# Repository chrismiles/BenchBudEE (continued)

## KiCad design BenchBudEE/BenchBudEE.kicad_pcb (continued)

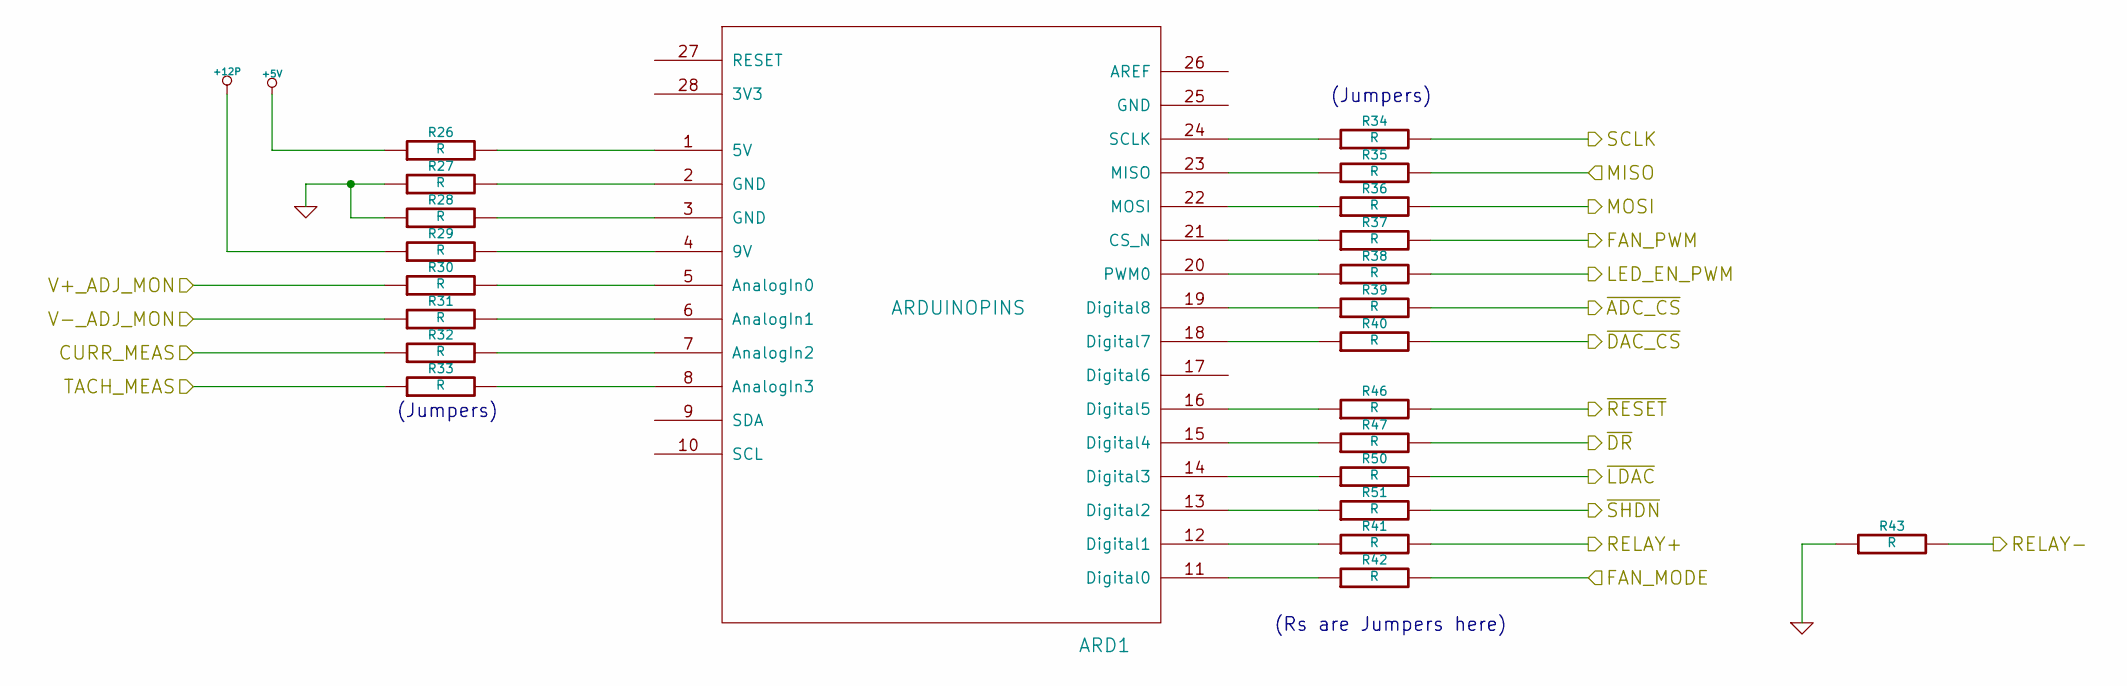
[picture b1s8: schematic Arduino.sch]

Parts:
ARD1: ARDUINOPINS
R26, R27, R28, R29, R30, R31, R32, R33, R34, R35, R36, R37, R38, R39, R40, R41, R42, R43, R46, R47, R50, R51: R

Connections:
+5V: R26.1; also elsewhere on the board
+12P: R29.1; also elsewhere on the board
/Arduino/CURR_MEAS: R32.1; also elsewhere on the board
/Arduino/FAN_MODE: R42.2; also elsewhere on the board
/Arduino/FAN_PWM: R37.2; also elsewhere on the board
/Arduino/LED_EN_PWM: R38.2; also elsewhere on the board
/Arduino/MISO: R35.2; also elsewhere on the board
/Arduino/MOSI: R36.2; also elsewhere on the board
/Arduino/RELAY+: R41.2; also elsewhere on the board
/Arduino/RELAY-: R43.2; also elsewhere on the board
/Arduino/SCLK: R34.2; also elsewhere on the board
/Arduino/V+_ADJ_MON: R30.1; also elsewhere on the board
/Arduino/V-_ADJ_MON: R31.1; also elsewhere on the board
/Arduino/~ADC_CS: R39.2; also elsewhere on the board
/Arduino/~DR: R47.2; also elsewhere on the board
/Arduino/~LDAC: R50.2; also elsewhere on the board
/Arduino/~RESET: R46.2; also elsewhere on the board
/Arduino/~SHDN: R51.2; also elsewhere on the board
/Fan/CS_N: R40.2; also elsewhere on the board
/Fan/TACH_IN: R33.1; also elsewhere on the board
GND: R27.1, R28.1, R43.1; also elsewhere on the board
unnamed: ARD1.7 (AnalogIn2), R32.2
unnamed: ARD1.8 (AnalogIn3), R33.2
unnamed: ARD1.21 (CS_N), R37.1
unnamed: ARD1.12 (Digital1), R41.1
unnamed: ARD1.6 (AnalogIn1), R31.2
unnamed: ARD1.5 (AnalogIn0), R30.2
unnamed: ARD1.1 (5V), R26.2
unnamed: ARD1.4 (9V), R29.2
unnamed: ARD1.3 (GND), R28.2
unnamed: ARD1.2 (GND), R27.2
unnamed: ARD1.20 (PWM0), R38.1
unnamed: ARD1.15 (Digital4), R47.1
unnamed: ARD1.18 (Digital7), R40.1
unnamed: ARD1.24 (SCLK), R34.1
unnamed: ARD1.14 (Digital3), R50.1
unnamed: ARD1.23 (MISO), R35.1
unnamed: ARD1.22 (MOSI), R36.1
unnamed: ARD1.11 (Digital0), R42.1
unnamed: ARD1.16 (Digital5), R46.1
unnamed: ARD1.13 (Digital2), R51.1
unnamed: ARD1.19 (Digital8), R39.1

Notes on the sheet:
(Rs are Jumpers here)
(Jumpers)

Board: 4 copper layers, 114 parts (50 on the bottom side), 98 nets, no tracks yet.

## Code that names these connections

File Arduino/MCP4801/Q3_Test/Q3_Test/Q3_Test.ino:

/*
  Q3 Test for BenchBudEE

*/


// inslude the SPI library:
#include <SPI.h>


// SPI
const int DAC_CS_N = 7;
const int SHDN_N = 2;

const int FAN_MODE = 3;

// PWM
const int FAN_PWM = 10;

void setup()
{
  pinMode (DAC_CS_N, OUTPUT);
  pinMode (FAN_MODE, OUTPUT);
  pinMode (SHDN_N, OUTPUT);
  
  // initialize SPI:
  SPI.setClockDivider(SPI_CLOCK_DIV128);
  SPI.setDataMode(SPI_MODE0);
  //SPI.setBitOrder(SPI_MSB_FIRST);
  SPI.begin();
  
  //Serial.begin(9600);
}

void loop()
{
  digitalWrite(SHDN_N, HIGH);
  digitalWrite(FAN_PWM, LOW);
  MCP4801Write(10);  // 10 = ~80mV
  
//  for (int pwm_level = 0; pwm_level < 4; pwm_level++) {
//    analogWrite(FAN_PWM, pwm_level * 64);
//    delay(5000);
//  }
  
//  analogWrite(FAN_PWM, 245);
  
  digitalWrite(FAN_MODE, HIGH);
  delay(8000);
  digitalWrite(FAN_MODE, LOW);
  delay(3000);
}

void MCP4801Write(int value)
{
  byte wr_enable = 0;
  byte ignored = 0;
  byte gain = 1;
  byte shdn = 1;
  
  int command = (wr_enable << 15) | (ignored << 14) | (gain << 13) | (shdn << 12)  | (value << 4);
  
  byte MSB = (command & 0xff00) >> 8;
  byte LSB = (command & 0x00ff);

  //Serial.print("value=");Serial.println(value);

  
  // take the CS pin low to select the chip:
  digitalWrite(DAC_CS_N, LOW);
   
  //  send data via SPI:
  SPI.transfer(MSB);
  SPI.transfer(LSB);
  
  // take the CS pin high to de-select the chip:
  digitalWrite(DAC_CS_N, HIGH);
}

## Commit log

2014-02-01 Created KiCad project with blank schematic and layout files.
2014-02-01 Created the main block hierarchy.
2014-02-01 Defined block inputs and outputs.
2014-02-05 Fleshed out the thermocouple sheet, in block form.
2014-02-06 Roughly filled in the Fan sheet.
2014-02-07 Roughly filled in the Relay sheet.
2014-02-08 Roughly populated the Power sheet.
2014-02-09 Populated the Power Adjustment Monitor sheet in rough form.
2014-02-09 Exposed hierarchical pins of Power Adjustment Monitor to top level sheet.
2014-02-10 Populated the LED Driver block based on the AP5726.
2014-02-10 Populated the Arduino block and top level wiring.
2014-02-12 Revisiting the current/fan module.
2014-02-12 Current/fan module refactoring.
2014-02-15 Added BOM and data sheets.
2014-02-15 Documented the fan driver mosfets.
2014-02-19 Connected Arduino power/ground. +5V power filtering. Removed current monitoring.
2014-02-20 Configured PCB and added board edges.
2014-02-20 Placed the relay components.
2014-02-21 Associated the Thermocouple components.
2014-02-21 Roughly placed the Thermocouple components.
2014-02-22 Associated the Terminal/ATX block components.
2014-02-22 Placed the Terminal/ATX block components.
2014-02-22 Associated and placed the Arduino module.
2014-02-22 Associating the current/fan driver module components.
2014-02-22 Roughly placed the current/fan driver module components.
2014-02-22 Associated components for the Power Protection and Filtering module.
2014-02-23 Roughly placed components for the Power Protection and Filtering module.
2014-02-23 Associated the power modification module components.
2014-02-23 Roughly placed the power modification module components.
2014-02-24 Associated the LED Driver module components.
2014-02-24 Roughly placed the LED Driver module components.
2014-07-15 Added Arduino sketches for relay & MCP4801.
2014-08-16 Updates MCP4801 PWM test Arduino sketch.
2014-08-16 Adds Q3 and Power Measure Arduino sketches.
2014-08-18 Adds MCP3901 register R/W test sketch.
2014-08-18 Adds MCP4801 fan control sketch.
2014-08-20 Fixes MCP3901 Register Read/Write Test sketch.
2015-07-26 Added LED_Test_PWM and MCP3901_Initial_Capture sketches.
